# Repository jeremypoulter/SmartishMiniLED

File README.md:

# SmartishNight
Electronics for a ESP32/NeoPixel based nightlight

| pin | output    |
|-----|-----------|
| 4   | Button    |
| 15  | IR        |
| 25  | Data out  |
| 32  | LED power |

## Enclosure

A parametric 3D printable case for the board lives in
[`enclosure/`](enclosure/): two parts that clip together, cable strain relief,
and no support material. There are three versions - USB-C port exposed,
hardwired power with a cable clamp, and a gasketed outdoor one.

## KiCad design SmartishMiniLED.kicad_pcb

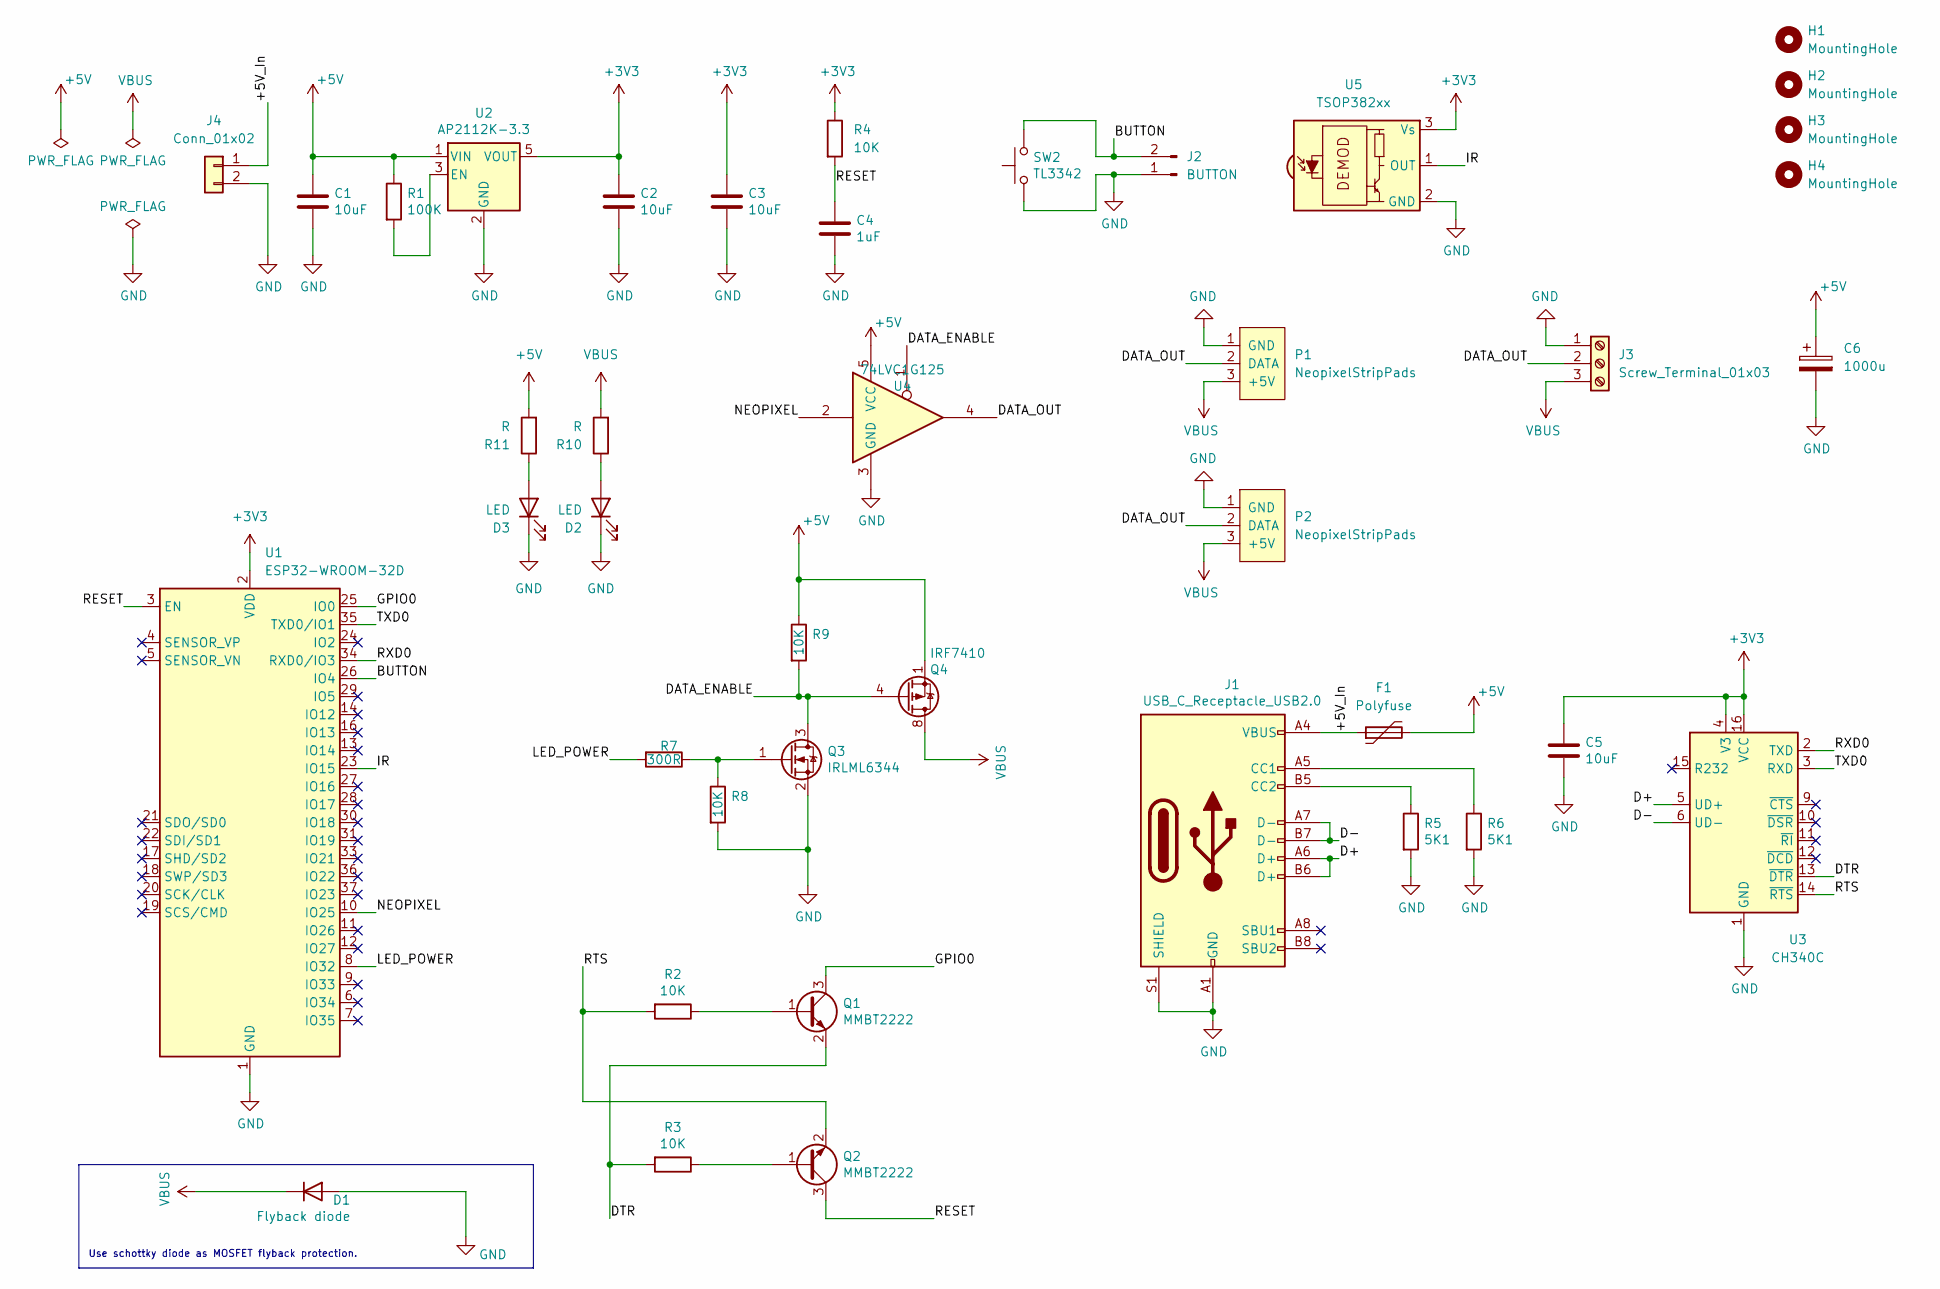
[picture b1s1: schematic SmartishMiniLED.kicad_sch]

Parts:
C1, C2, C3, C5: 10uF; C_0805_2012Metric; LCSC C15850
C4: 1uF; C_0805_2012Metric; LCSC C15850
C6: 1000u; CP_Elec_10x10; LCSC C176684
D1: Flyback diode; D_SMA_Handsoldering; LCSC C2480
D2, D3: LED; LED_0805_2012Metric
F1: Polyfuse; Fuse_1206_3216Metric; LCSC C207041
H1, H2, H3, H4: MountingHole; MountingHole_3.2mm_M3
J1: USB_C_Receptacle_USB2.0; USB_C_Receptacle_HRO_TYPE-C-31-M-12; LCSC C165948
J2: BUTTON; PinHeader_1x02_P2.54mm_Vertical
J3: Screw_Terminal_01x03; TerminalBlock_TE_282834-3_1x03_P2.54mm_Horizontal
J4: Conn_01x02; Main_Power
P1, P2: NeopixelStripPads; LedStripPads
Q1, Q2: MMBT2222; SOT-23; LCSC C2891810
Q3: IRLML6344; SOT-23; LCSC C693370
Q4: IRF7410; SOIC-8_3.9x4.9mm_P1.27mm; LCSC C148144
R1: 100K; R_0805_2012Metric; LCSC C149504
R2, R3, R8, R9: 10K; R_0805_2012Metric; LCSC C17414
R4: 10K; R_0805_2012Metric
R5, R6: 5K1; R_0805_2012Metric; LCSC C27834
R7: 300R; R_0805_2012Metric; LCSC C352224
R10, R11: R; R_0805_2012Metric
SW2: TL3342; SW_SPST_TL3342; LCSC C318884
U1: ESP32-WROOM-32D; LCSC C473012
U2: AP2112K-3.3; SOT-23-5; LCSC C51118
U3: CH340C; SOIC-16_3.9x9.9mm_P1.27mm; LCSC C84681
U4: 74LVC1G125; SOT-23-5; LCSC C23654
U5: TSOP382xx; Vishay_MINICAST-3Pin

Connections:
+3V3: C2.1, C3.1, C5.1, R4.1, U1.2 (VDD), U2.5 (VOUT), U3.4 (V3), U3.16 (VCC), U5.3 (Vs)
+5V: C1.1, C6.1, F1.2, Q4.1 (S), Q4.2 (S), Q4.3 (S), R1.1, R9.1, R11.2, U2.1 (VIN), U4.5 (VCC)
/+5V_In: F1.1, J1.A4 (VBUS), J1.A9 (VBUS), J1.B4 (VBUS), J1.B9 (VBUS), J4.1
/BUTTON: J2.2, SW2.2, U1.26 (IO4)
/D+: J1.A6 (D+), J1.B6 (D+), U3.5 (UD+)
/D-: J1.A7 (D-), J1.B7 (D-), U3.6 (UD-)
/DATA_ENABLE: Q3.3 (D), Q4.4 (G), R9.2, U4.1
/DATA_OUT: J3.2, P1.2 (DATA), P2.2 (DATA), U4.4
/DTR: Q1.2 (E), R3.2, U3.13 (~DTR)
/GPIO0: Q1.3 (C), U1.25 (IO0)
/IR: U1.23 (IO15), U5.1 (OUT)
/LED_POWER: R7.2, U1.8 (IO32)
/NEOPIXEL: U1.10 (IO25), U4.2
/RESET: C4.1, Q2.3 (C), R4.2, U1.3 (EN)
/RTS: Q2.2 (E), R2.2, U3.14 (~RTS)
/RXD0: U1.34 (RXD0/IO3), U3.2 (TXD)
/TXD0: U1.35 (TXD0/IO1), U3.3 (RXD)
GND: C1.2, C2.2, C3.2, C4.2, C5.2, C6.2, D1.2 (A), D2.1 (K), D3.1 (K), J1.A1 (GND), J1.A12 (GND), J1.B1 (GND), J1.B12 (GND), J1.S1 (SHIELD), J2.1, J3.1, J4.2, P1.1 (GND), P2.1 (GND), Q3.2 (S), R5.2, R6.2, R8.2, SW2.1, U1.1 (GND), U1.15 (GND), U1.38 (GND), U1.39 (GND), U2.2 (GND), U3.1 (GND), U4.3 (GND), U5.2 (GND)
unnamed: D2.2 (A), R10.1
unnamed: D3.2 (A), R11.1
unnamed: J1.A5 (CC1), R6.1
unnamed: J1.B5 (CC2), R5.1
unnamed: Q1.1 (B), R2.1
unnamed: Q2.1 (B), R3.1
unnamed: Q3.1 (G), R7.1, R8.1
unnamed: R1.2, U2.3 (EN)
VBUS: D1.1 (K), J3.3, P1.3 (+5V), P2.3 (+5V), Q4.5 (D), Q4.6 (D), Q4.7 (D), Q4.8 (D), R10.2

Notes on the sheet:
Use schottky diode as MOSFET flyback protection.

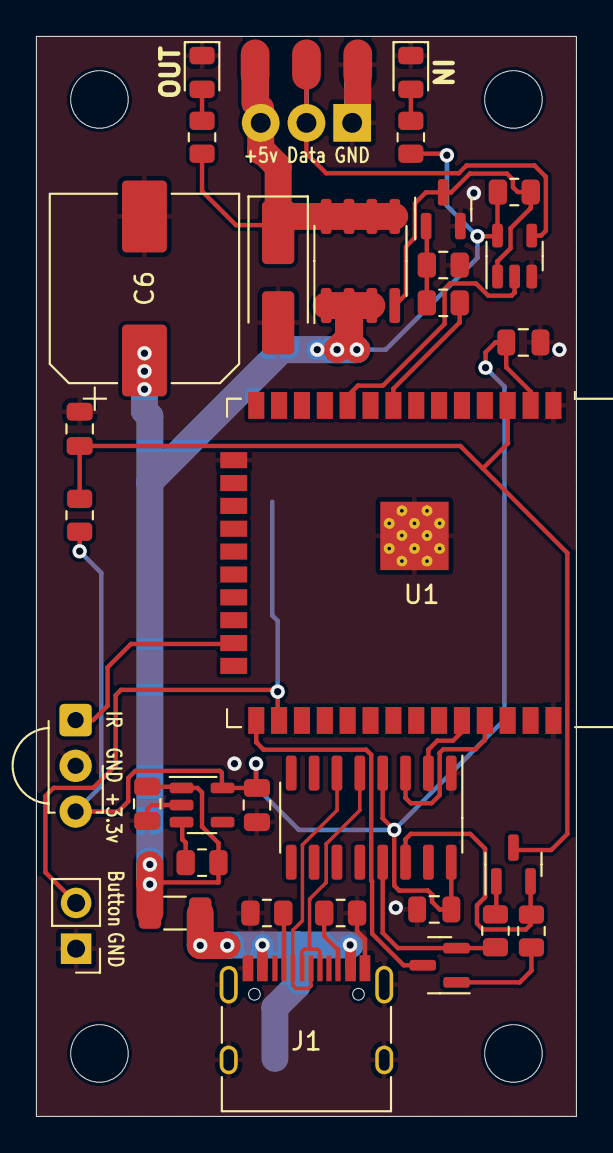
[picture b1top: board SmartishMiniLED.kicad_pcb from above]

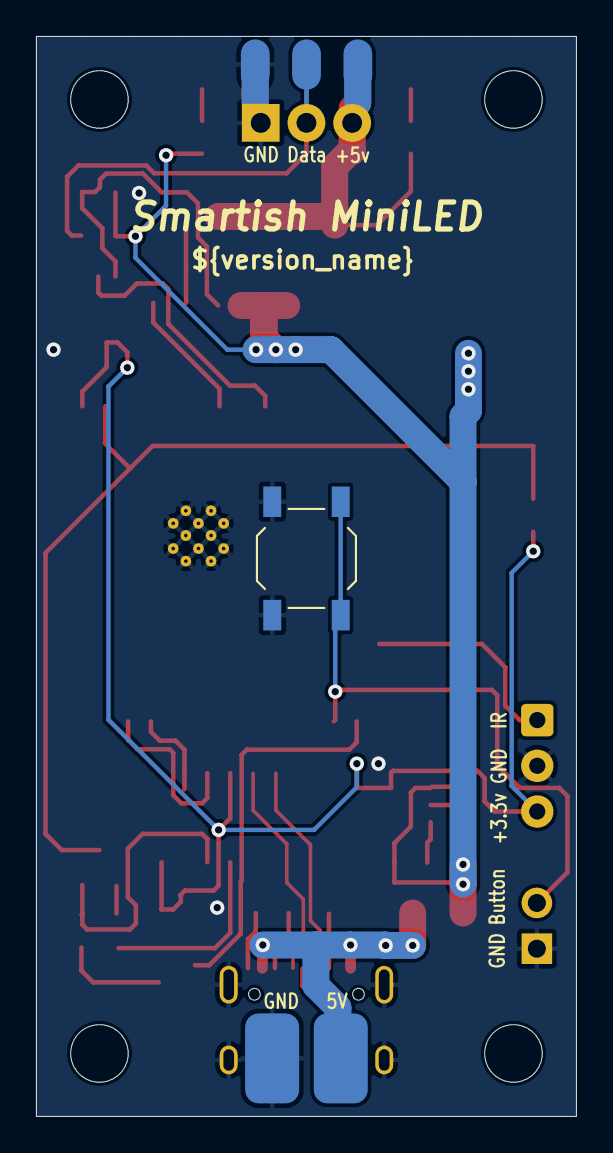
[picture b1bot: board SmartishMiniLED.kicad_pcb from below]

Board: 2 copper layers, 30.0 x 60.0 mm, 41 parts (3 on the bottom side), 27 nets.

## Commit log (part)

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2022-06-21 Initial import
    Basically a copy of the SmartishNight project with the LEDs removed and a few additional components added (schematic only)
2022-06-29 Remove old v5 files
2022-06-29 Added MOSFET to switch LED power and fixed ERC errors
2022-07-26 WIP Fixed a few bugs in schematic and made a start on the PCB layout
2022-07-26 Workflow fixes (hopefully)
2022-08-01 Initial layout
2022-08-02 DRC check fixes
2022-08-02 DRC fix
2022-08-02 2nd attempt to fix DRC errors
2022-08-02 Updated kibot workflow
2022-08-03 Fixing doc steps
2022-08-03 Wait on DRC for fabrication files
2022-08-03 Increased main power line to 1.5mm, should handle 3A
2022-08-03 Added some id text
2022-08-03 Corrected Docker version
2022-08-03 A few fixes and tidy ups
2022-08-03 Fix DRC warnings
2022-08-15 Added some pads on the back for as an alternative to supplying the main power.
2022-08-20 Updates for production
2022-08-20 Fixed DRC errors
2022-08-21 Reworked using the WROOM-32D module
    This allows for easier manufacrure
2022-08-21 Fixed 3D models
2022-08-23 Added LCSC part numbers
2022-08-23 Part position corrections
2022-08-23 More position updates
2022-08-23 Fix for release workflow
2022-08-23 Fix number 2 for release
2022-08-24 Updated position corrections
2022-08-24 Stopped putting vias directly on pads, can cause productions errors
2022-08-24 Updated teh version number
2022-10-17 Added generation of the step file to help with enclosure design
2022-10-17 The docs depend on both ERC and DRC
2022-10-17 Updated to latest actions and corrected docs release
2022-10-25 Adding the USB C connector
2022-10-25 Set the top layer as the default
2022-10-25 Moved to the official KiBot GitHub Action
2022-10-25 Missed specifying the config
2022-10-25 Stop using the wildcards to solve build error
2022-10-25 Typo fix
2023-11-09 Add auto-saved files to .gitignore.
2023-11-09 Various fixes
    - Moved the capacitor to the other side of the MOSFET to fix brownout issues, fixes #4
    - Added extra components needed to fix restart when programming via USB, fixes #2
2023-11-09 Adding some power LEDs to help diagnose power issues.
    Also various fixes to checks.
2023-11-28 DRC fixes
2023-11-28 Updated to use KiCAD v7
2023-11-28 Fix KiKit fabrication
2023-11-28 Updated to v7
2024-04-06 Added pinout
